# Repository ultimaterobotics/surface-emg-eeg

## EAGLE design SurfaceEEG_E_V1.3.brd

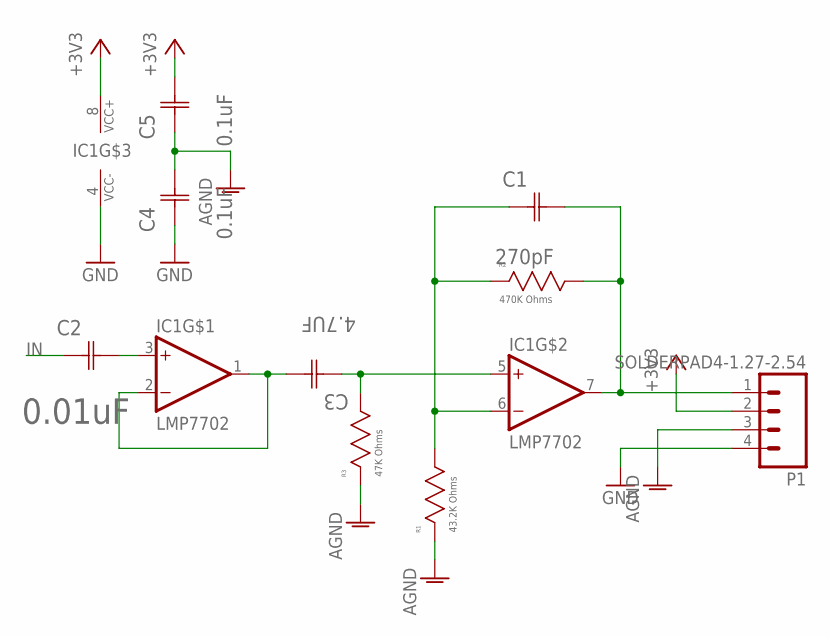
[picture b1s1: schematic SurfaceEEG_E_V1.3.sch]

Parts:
C1: 270pF; CAPC1608X90N
C2: 0.01uF; CAPC1005X60N
C3: 4.7UF; CAPC1608X90N
C4, C5: 0.1uF; CAPC1005X60N
IC1: LMP7702; VSSOP8
P1: SOLDERPAD4-1.27-2.54; SMD1,27-2,54
R1: 43.2K Ohms; RESC1608X60N
R2: 470K Ohms; RESC1608X60N
R3: 47K Ohms; RESC1608X60N

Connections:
+3V3: C5.1 (C2), IC1.8 (VCC+), P1.2
AGND: C4.1 (C2), C5.2 (C1), P1.3, R1.2 (R2), R3.2 (R2)
GND: C4.2 (C1), IC1.4 (VCC-), P1.4
IN: C2.1 (C1)
unnamed: C2.2 (C2), IC1.3 (IN+)
unnamed: C1.1 (C1), IC1.6 (IN-), R1.1 (R1), R2.2 (R2)
unnamed: C3.1 (C1), IC1.5 (IN+), R3.1 (R1)
unnamed: C1.2 (C2), IC1.7 (OUT), P1.1, R2.1 (R1)
SHIELD: C3.2 (C2), IC1.1 (OUT), IC1.2 (IN-)

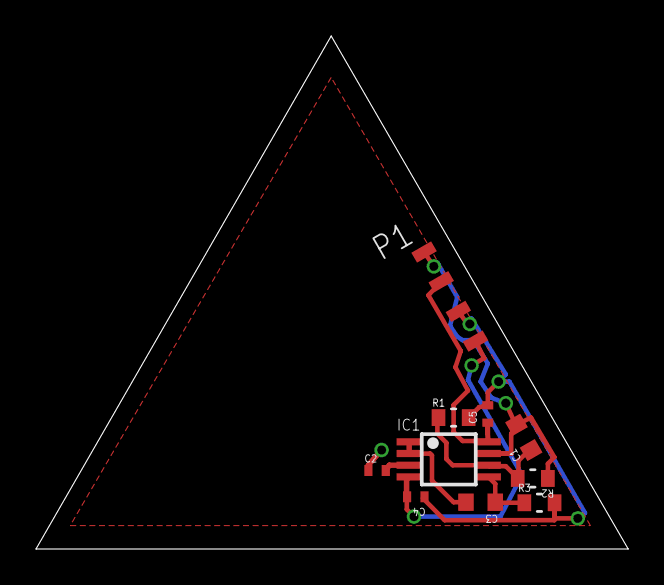
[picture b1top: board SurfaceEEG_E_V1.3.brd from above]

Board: 2 copper layers, 32.9 x 28.5 mm, 10 parts (0 on the bottom side), 8 nets.

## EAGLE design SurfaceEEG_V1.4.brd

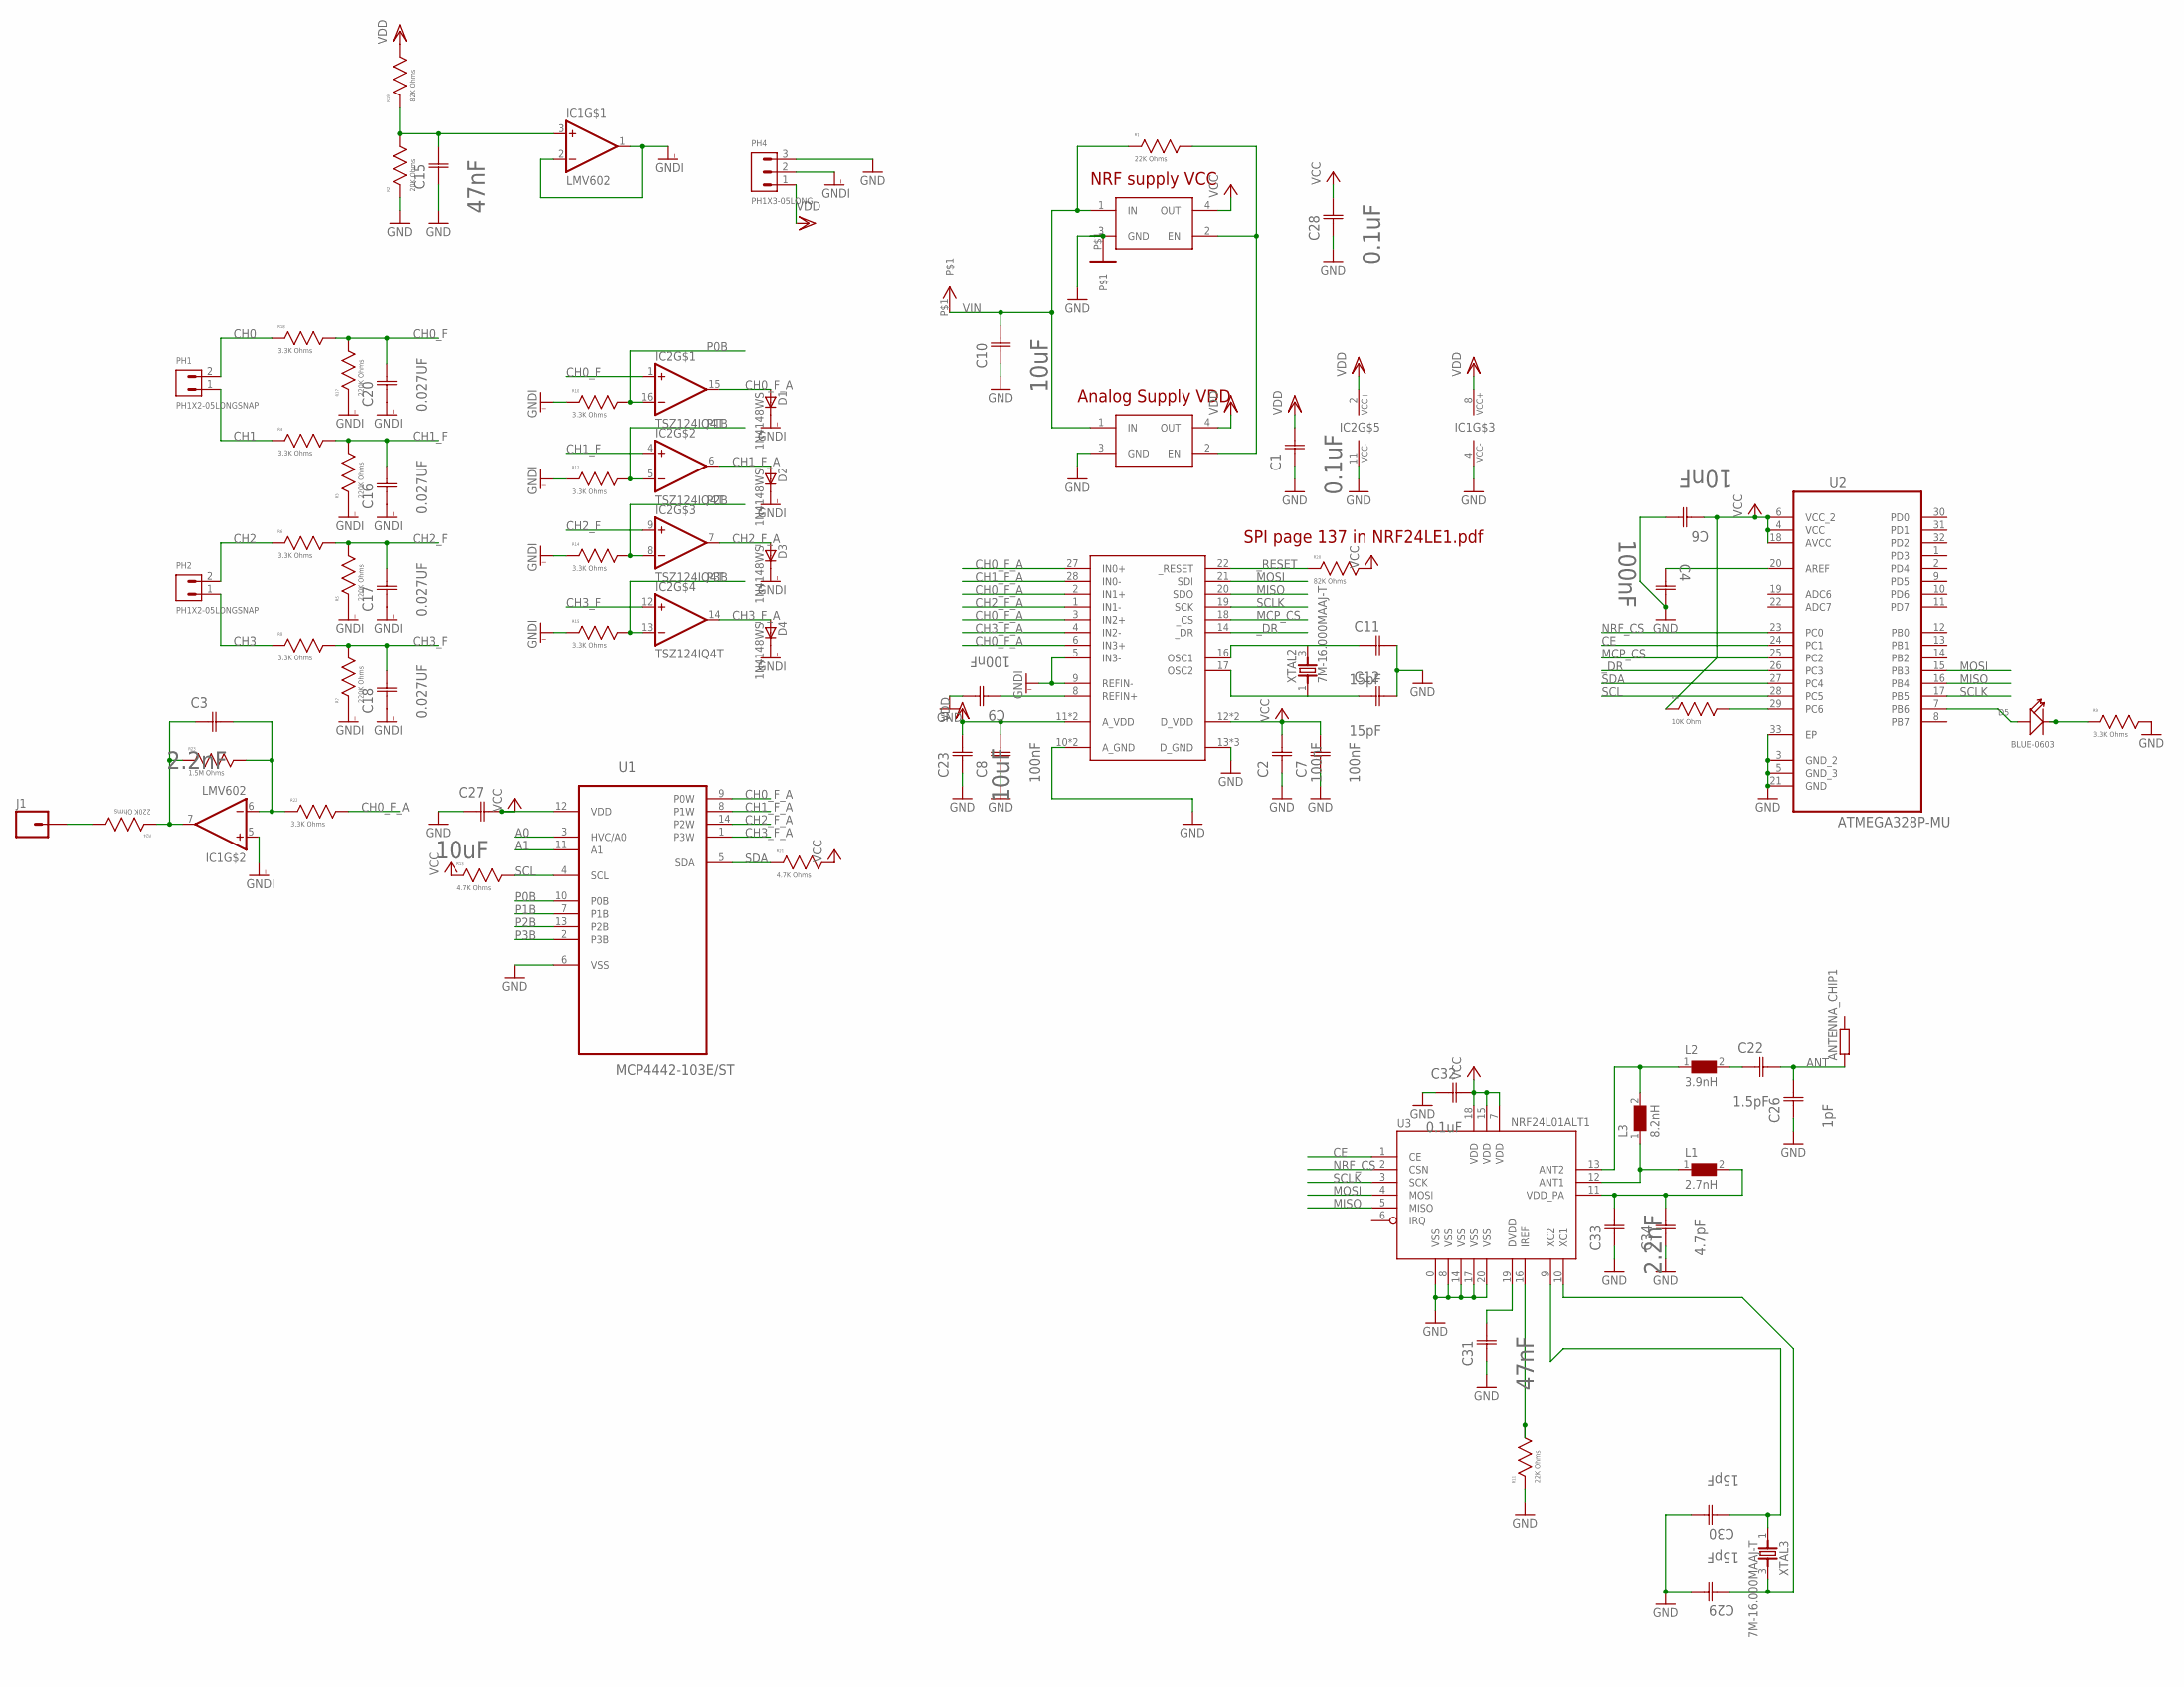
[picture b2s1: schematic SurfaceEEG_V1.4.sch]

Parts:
ANTENNA_CHIP1: R0805
C1, C28: 0.1uF; CAPC1608X85N
C2, C7, C8, C9: 100nF; CAPC1608X90N
C3, C33: 2.2nF; CAPC1005X60N
C4: 100nF; CAPC1608X85N
C6: 10nF; CAPC1608X85N
C10, C23, C27: 10uF; CAPC1608X85N
C11, C12, C29, C30: 15pF; CAPC1005X60N
C15, C31: 47nF; CAPC1608X85N
C16, C17, C18, C20: 0.027UF; CAPC1608X90N
C22: 1.5pF; CAPC1005X60N
C26: 1pF; CAPC1005X60N
C32: 0.1uF; CAPC1005X60N
C34: 4.7pF; CAPC1005X60N
D1, D2, D3, D4: 1N4148WS; SOD323F
D5: BLUE-0603; LED-0603
IC1: LMV602; VSSOP8
IC2: TSZ124IQ4T; QFN16
J1: M01SMD-4.5X1.5; PAD-1.5X4.5
L1: 2.7nH; WE-KI_0402A
L2: 3.9nH; WE-KI_0402A
L3: 8.2nH; WE-KI_0402A
PH1, PH2: PH1X2-05LONGSNAP; PHLS005-1-2
PH4: PH1X3-05LONG; PHL005-1-3
R1, R11: 22K Ohms; RESC1608X60N
R2: 20K Ohms; RESC1608X60N
R3, R5, R7, R17, R24: 220K Ohms; RESC1608X60N
R4, R6, R8, R9, R10, R12, R14, R15, R18, R22: 3.3K Ohms; RESC1608X60N
R13, R21: 4.7K Ohms; RESC1005X40N
R16: 10K Ohm; RESC1608X60N
R19, R20: 82K Ohms; RESC1608X60N
R23: 1.5M Ohms; RESC1608X60N
U1: MCP4442-103E/ST; SOP65P640X120-14N
U2: ATMEGA328P-MU; QFN50P500X500X100-33N
U3: NRF24L01ALT1; QFN20_ALT1
U$1, U$2: NCP103; UDFN4-1*1
U$3: MCP3912; QFN28
U$4: VCC; VCC-PAD
U$5: GND; GND-PAD
XTAL2, XTAL3: 7M-16.000MAAJ-T; TXC_7M-16.000MAAJ-T

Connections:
A0: U1.3 (HVC/A0)
A1: U1.11 (A1)
ANT: ANTENNA_CHIP1.1, C22.1 (C2), C26.1 (C2)
ANT1: L1.1, L3.1, U3.12 (ANT1)
ANT2: L2.1, L3.2, U3.13 (ANT2)
CE: U2.24 (PC1), U3.1 (CE)
CH0: PH1.2, R18.2 (R2)
CH0_F: C20.2 (C2), IC2.1 (IN+), R17.1 (R1), R18.1 (R1)
CH0_F_A: D1.A, IC2.15 (OUT), R22.1 (R1), U1.9 (P0W), U$3.2 (IN1+), U$3.3 (IN2+), U$3.6 (IN3+), U$3.27 (IN0+)
CH1: PH1.1, R4.2 (R2)
CH1_F: C16.2 (C2), IC2.4 (IN+), R3.1 (R1), R4.1 (R1)
CH1_F_A: D2.A, IC2.6 (OUT), U1.8 (P1W), U$3.28 (IN0-)
CH2: PH2.2, R6.2 (R2)
CH2_F: C17.2 (C2), IC2.9 (IN+), R5.1 (R1), R6.1 (R1)
CH2_F_A: D3.A, IC2.7 (OUT), U1.14 (P2W), U$3.1 (IN1-)
CH3: PH2.1, R8.2 (R2)
CH3_F: C18.2 (C2), IC2.12 (IN+), R7.1 (R1), R8.1 (R1)
CH3_F_A: D4.A, IC2.14 (OUT), U1.1 (P3W), U$3.4 (IN2-)
GND: C1.1 (C1), C2.1 (C1), C4.2 (C2), C6.2 (C2), C7.1 (C1), C8.1 (C1), C9.2 (C2), C10.1 (C1), C11.1 (C2), C12.1 (C2), C15.1 (C1), C23.1 (C1), C26.2 (C1), C27.1 (C1), C28.1 (C1), C29.1 (C2), C30.1 (C2), C31.1 (C1), C32.2 (C1), C33.1 (C1), C34.2 (C1), IC1.4 (VCC-), IC2.11 (VCC-), PH4.3, R2.2 (R2), R9.1 (R1), R11.2 (R2), U1.6 (VSS), U2.3 (GND_2), U2.5 (GND_3), U2.21 (GND), U2.33 (EP), U3.0 (VSS), U3.8 (VSS), U3.14 (VSS), U3.17 (VSS), U3.20 (VSS), U$1.3 (GND), U$2.3 (GND), U$3.10 (A_GND), U$3.13 (D_GND), U$3.15 (D_GND), U$3.23 (D_GND), U$3.26 (A_GND), U$5.P$1
GNDI: C16.1 (C1), C17.1 (C1), C18.1 (C1), C20.1 (C1), D1.C, D2.C, D3.C, D4.C, IC1.1 (OUT), IC1.2 (IN-), IC1.5 (IN+), PH4.2, R3.2 (R2), R5.2 (R2), R7.2 (R2), R10.2 (R2), R12.2 (R2), R14.2 (R2), R15.2 (R2), R17.2 (R2), U$3.5 (IN3-), U$3.9 (REFIN-)
MCP_CS: U2.25 (PC2), U$3.18 (_CS)
MISO: U2.16 (PB4), U3.5 (MISO), U$3.20 (SDO)
MOSI: U2.15 (PB3), U3.4 (MOSI), U$3.21 (SDI)
unnamed: D5.+, U2.7 (PB6)
unnamed: D5.-, R9.2 (R2)
unnamed: C3.2 (C2), IC1.6 (IN-), R22.2 (R2), R23.1 (R1)
unnamed: R1.1 (R1), U$1.2 (EN), U$2.2 (EN)
unnamed: C3.1 (C1), IC1.7 (OUT), R23.2 (R2), R24.2 (R2)
unnamed: C4.1 (C1), U2.20 (AREF)
unnamed: C30.2 (C1), U3.9 (XC2), XTAL3.1
unnamed: C29.2 (C1), U3.10 (XC1), XTAL3.3
unnamed: J1.P$1, R24.1 (R1)
unnamed: C9.1 (C1), U$3.8 (REFIN+)
unnamed: C22.2 (C1), L2.2
unnamed: C11.2 (C1), U$3.16 (OSC1), XTAL2.3
unnamed: C12.2 (C1), U$3.17 (OSC2), XTAL2.1
unnamed: C33.2 (C2), C34.1 (C2), L1.2, U3.11 (VDD_PA)
unnamed: C15.2 (C2), IC1.3 (IN+), R2.1 (R1), R19.2 (R2)
unnamed: R11.1 (R1), U3.16 (IREF)
unnamed: C31.2 (C2), U3.19 (DVDD)
NRF_CS: U2.23 (PC0), U3.2 (CSN)
P0B: IC2.16 (IN-), R10.1 (R1), U1.10 (P0B)
P1B: IC2.5 (IN-), R12.1 (R1), U1.7 (P1B)
P2B: IC2.8 (IN-), R14.1 (R1), U1.13 (P2B)
P3B: IC2.13 (IN-), R15.1 (R1), U1.2 (P3B)
RESET: R16.1 (R1), U2.29 (PC6)
SCL: R13.1 (R1), U1.4 (SCL), U2.28 (PC5)
SCLK: U2.17 (PB5), U3.3 (SCK), U$3.19 (SCK)
SDA: R21.2 (R2), U1.5 (SDA), U2.27 (PC4)
VCC: C2.2 (C2), C6.1 (C1), C7.2 (C2), C27.2 (C2), C28.2 (C2), C32.1 (C2), R13.2 (R2), R16.2 (R2), R20.1 (R1), R21.1 (R1), U1.12 (VDD), U2.4 (VCC), U2.6 (VCC_2), U2.18 (AVCC), U3.7 (VDD), U3.15 (VDD), U3.18 (VDD), U$1.4 (OUT), U$3.12 (D_VDD), U$3.24 (D_VDD)
VDD: C1.2 (C2), C8.2 (C2), C23.2 (C2), IC1.8 (VCC+), IC2.2 (VCC+), PH4.1, R19.1 (R1), U$2.4 (OUT), U$3.11 (A_VDD), U$3.25 (A_VDD)
VIN: C10.2 (C2), R1.2 (R2), U$1.1 (IN), U$2.1 (IN), U$4.P$1
_DR: U2.26 (PC3), U$3.14 (_DR)
_RESET: R20.2 (R2), U$3.22 (_RESET)

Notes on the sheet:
SPI page 137 in NRF24LE1.pdf
NRF supply VCC
Analog Supply VDD

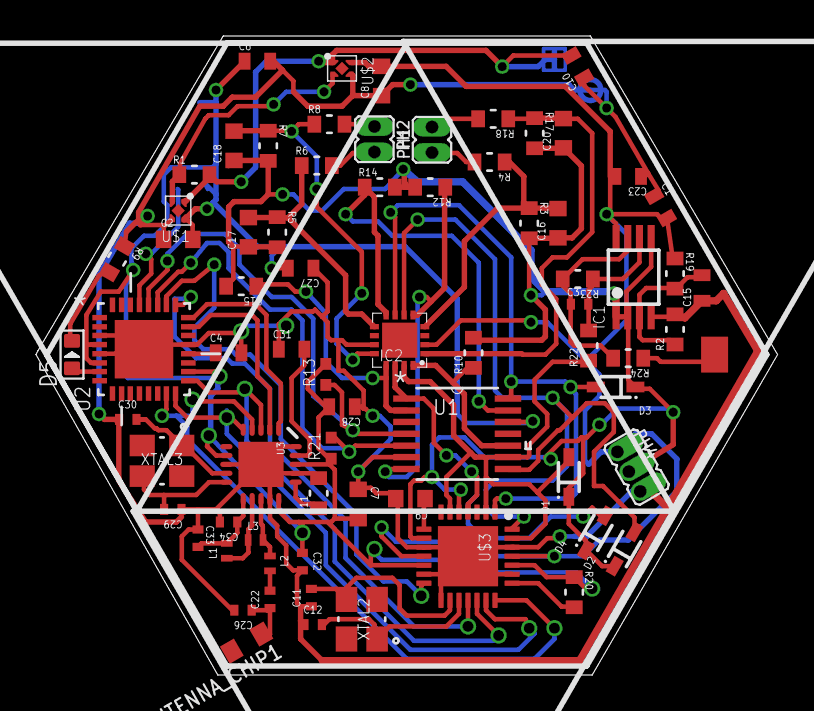
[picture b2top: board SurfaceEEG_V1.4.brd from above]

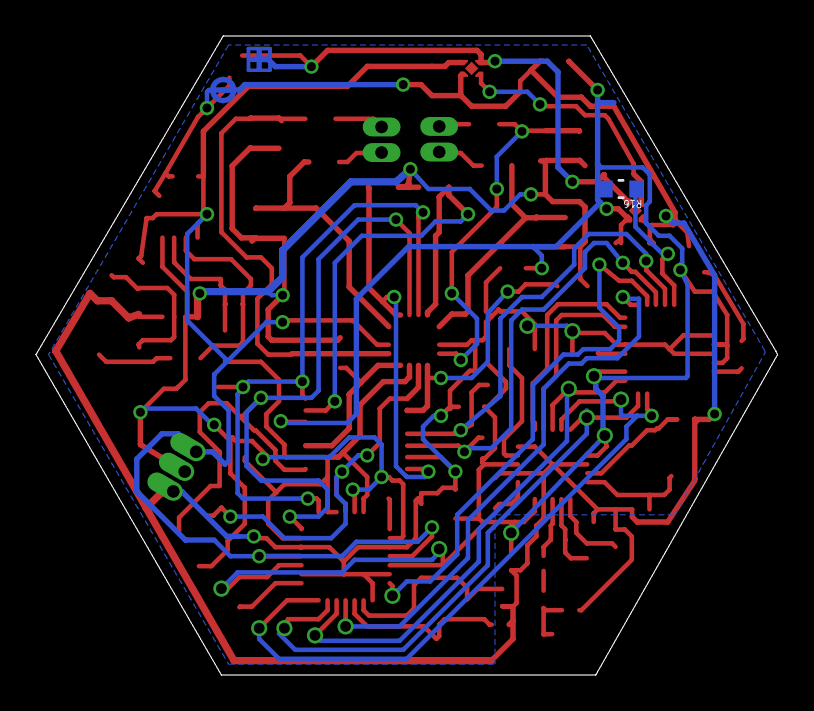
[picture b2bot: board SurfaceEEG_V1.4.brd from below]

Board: 2 copper layers, 41.2 x 35.5 mm, 76 parts (3 on the bottom side), 52 nets.

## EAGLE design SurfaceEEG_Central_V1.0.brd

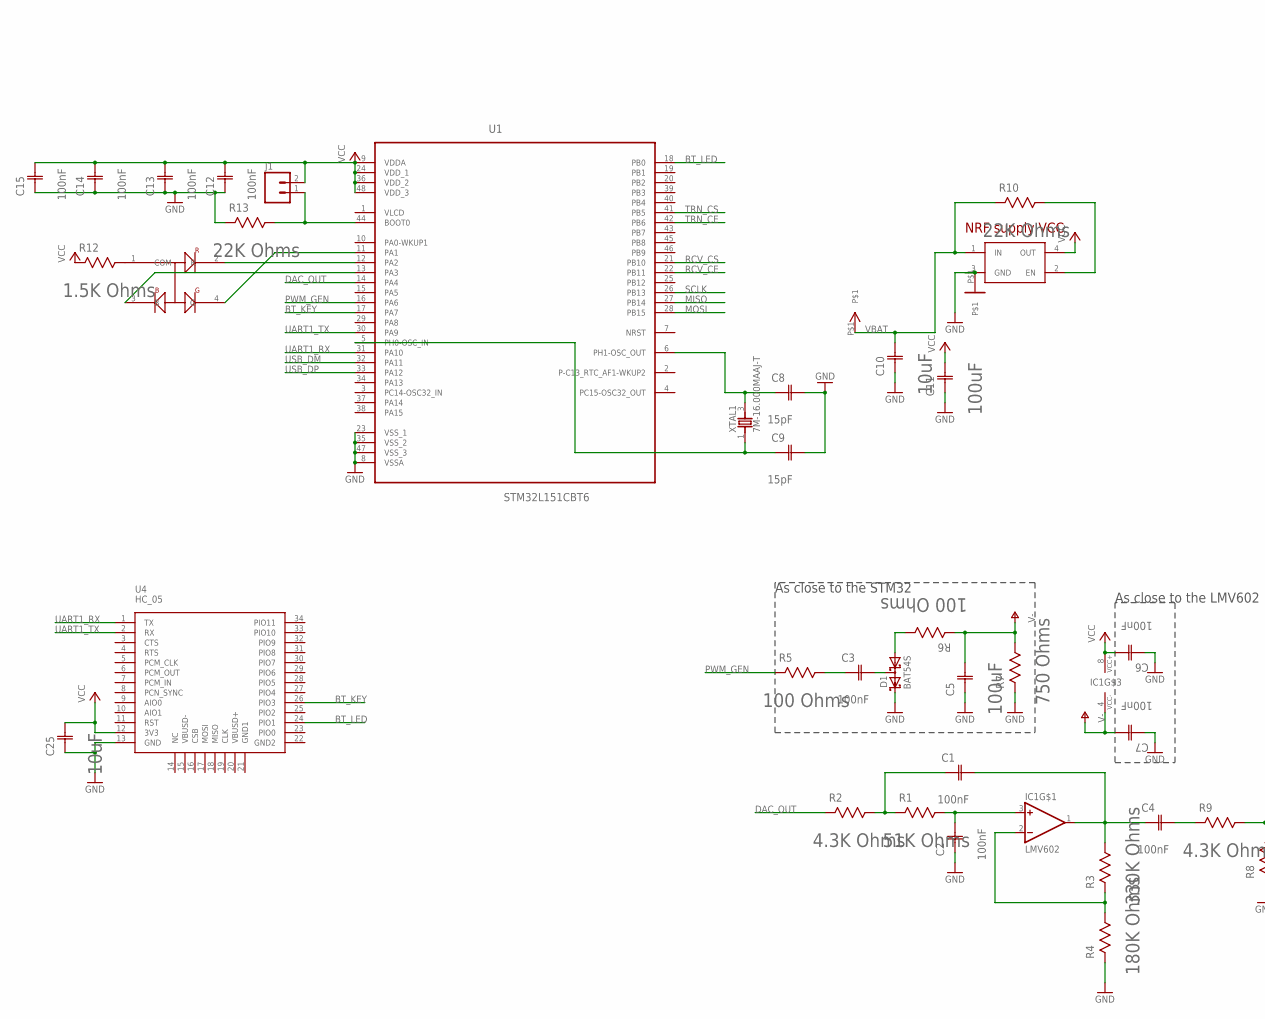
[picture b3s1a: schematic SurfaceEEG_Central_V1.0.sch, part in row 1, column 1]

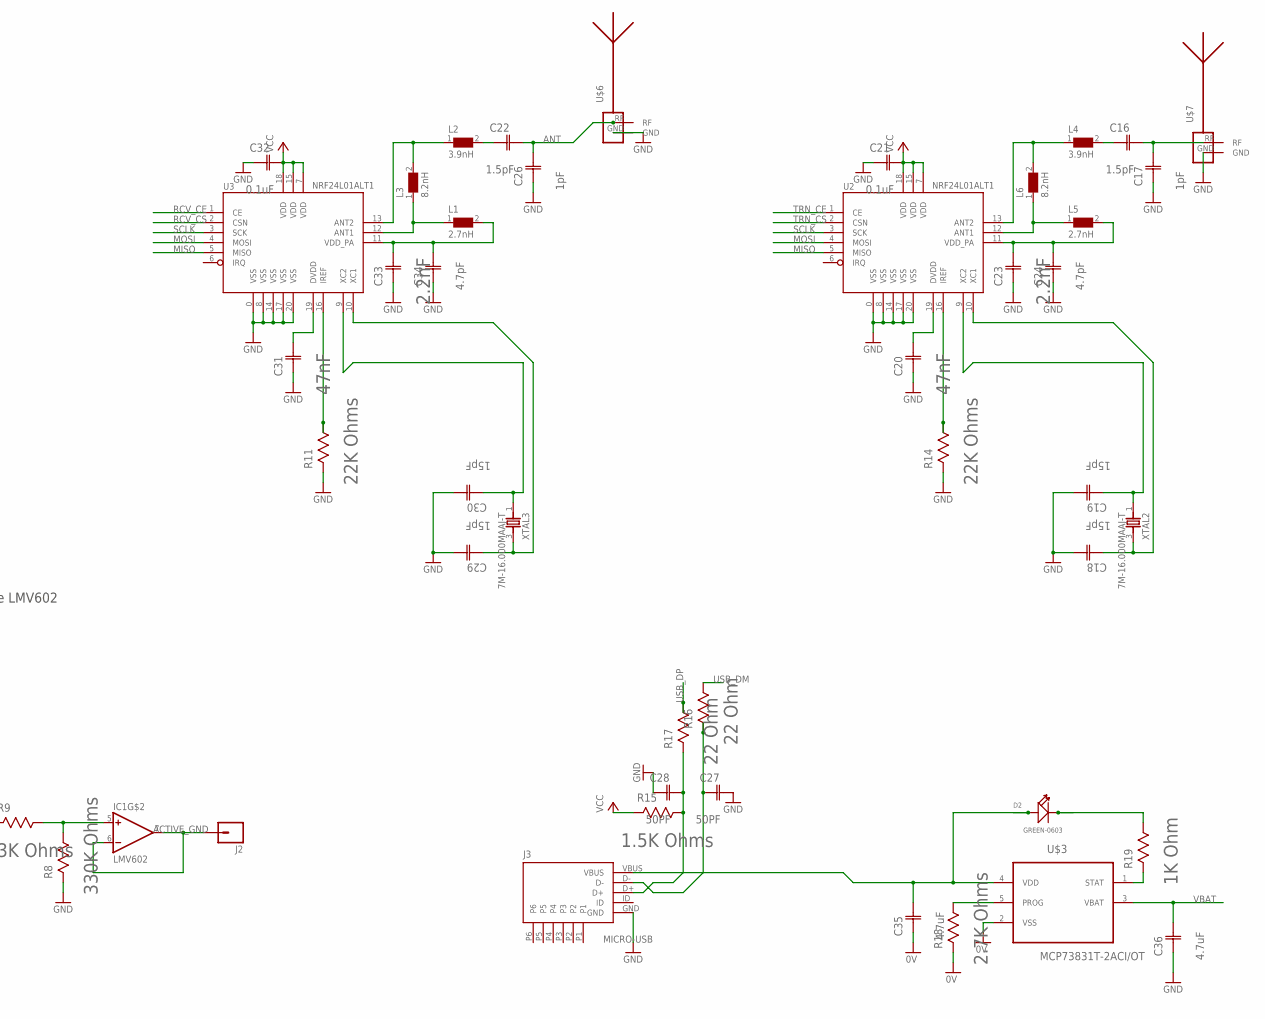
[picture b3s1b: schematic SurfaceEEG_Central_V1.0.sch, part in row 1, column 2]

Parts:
C1, C2, C3, C4, C6, C7, C12, C13, C14, C15: 100nF; CAPC1608X90N
C5, C11: 100uF; CAPC3216X180N
C8, C9, C18, C19, C29, C30: 15pF; CAPC1005X60N
C10, C25: 10uF; CAPC1608X85N
C16, C22: 1.5pF; CAPC1005X60N
C17, C26: 1pF; CAPC1005X60N
C20, C31: 47nF; CAPC1608X85N
C21, C32: 0.1uF; CAPC1005X60N
C23, C33: 2.2nF; CAPC1005X60N
C24, C34: 4.7pF; CAPC1005X60N
C27, C28: 50PF; CAPC1608X90N
C35, C36: 4.7uF; CAPC2013X152N
D1: BAT54S; SOT23
D2: GREEN-0603; LED-0603
IC1: LMV602; VSSOP8
J1: M02PTH; 1X02
J2: M01SMD-4.5X1.5; PAD-1.5X4.5
J3: MICRO-USB; MICRO_USB
L1, L5: 2.7nH; WE-KI_0402A
L2, L4: 3.9nH; WE-KI_0402A
L3, L6: 8.2nH; WE-KI_0402A
R1: 51K Ohms; RESC1608X60N
R2, R9: 4.3K Ohms; RESC1608X60N
R3, R8: 330K Ohms; RESC1608X60N
R4: 180K Ohms; RESC1608X60N
R5, R6: 100 Ohms; RESC1608X60N
R7: 750 Ohms; RESC1608X60N
R10, R11, R13, R14: 22K Ohms; RESC1608X60N
R12, R15: 1.5K Ohms; RESC1608X60N
R16, R17: 22 Ohm; RESC1608X60N
R18: 2.7K Ohms; RESC1608X60N
R19: 1K Ohm; RESC1608X60N
U1: STM32L151CBT6; QFP50P900X900X160-48N
U2, U3: NRF24L01ALT1; QFN20_ALT1
U4: HC_05; BLUETOOTH_SMD
U$1: NCP103; UDFN4-1*1
U$2: RGB-LED; 1615-RGB-LED
U$3: MCP73831T-2ACI/OT; SOT95P280X145-5N
U$4: VCC; VCC-PAD
U$5: GND; GND-PAD
U$6: ANTENNA_1LEFT; SWRA117D_LEFT
U$7: ANTENNA_1RIGHT; SWRA117D_RIGHT
XTAL1, XTAL2, XTAL3: 7M-16.000MAAJ-T; TXC_7M-16.000MAAJ-T

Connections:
0V: C35.1 (C1), R18.2 (R2), U$3.2 (VSS)
ACTIVE_GND: IC1.6 (IN-), IC1.7 (OUT), J2.P$1
ANT: C22.1 (C2), C26.1 (C2), U$6.RF
ANT1: L1.1, L3.1, U3.12 (ANT1)
ANT2: L2.1, L3.2, U3.13 (ANT2)
ANT3: L4.1, L6.2, U2.13 (ANT2)
ANT4: L5.1, L6.1, U2.12 (ANT1)
BT_KEY: U1.17 (PA7), U4.26 (PIO3)
BT_LED: U1.18 (PB0), U4.24 (PIO1)
DAC_OUT: R2.2 (R2), U1.14 (PA4)
GND: C2.1 (C1), C5.1 (C1), C6.1 (C1), C7.1 (C1), C8.1 (C2), C9.1 (C2), C10.1 (C1), C11.1 (C1), C12.1 (C1), C13.1 (C1), C14.1 (C1), C15.1 (C1), C17.2 (C1), C18.1 (C2), C19.1 (C2), C20.1 (C1), C21.2 (C1), C23.1 (C1), C24.2 (C1), C25.1 (C1), C26.2 (C1), C27.2 (C2), C28.1 (C1), C29.1 (C2), C30.1 (C2), C31.1 (C1), C32.2 (C1), C33.1 (C1), C34.2 (C1), C36.1 (C1), D1.2 (C2), J3.GND, R4.2 (R2), R7.2 (R2), R8.2 (R2), R11.2 (R2), R13.2 (R2), R14.2 (R2), U1.8 (VSSA), U1.23 (VSS_1), U1.35 (VSS_2), U1.47 (VSS_3), U2.0 (VSS), U2.8 (VSS), U2.14 (VSS), U2.17 (VSS), U2.20 (VSS), U3.0 (VSS), U3.8 (VSS), U3.14 (VSS), U3.17 (VSS), U3.20 (VSS), U4.13 (GND), U$1.3 (GND), U$5.P$1, U$6.GND, U$7.GND
MISO: U1.27 (PB14), U2.5 (MISO), U3.5 (MISO)
MOSI: U1.28 (PB15), U2.4 (MOSI), U3.4 (MOSI)
unnamed: C1.1 (C1), R1.2 (R2), R2.1 (R1)
unnamed: IC1.2 (IN-), R3.2 (R2), R4.1 (R1)
unnamed: C1.2 (C2), C4.1 (C1), IC1.1 (OUT), R3.1 (R1)
unnamed: C2.2 (C2), IC1.3 (IN+), R1.1 (R1)
unnamed: IC1.5 (IN+), R8.1 (R1), R9.1 (R1)
unnamed: C4.2 (C2), R9.2 (R2)
unnamed: C3.1 (C1), R5.1 (R1)
unnamed: C3.2 (C2), D1.3 (C1A2)
unnamed: D1.1 (A1), R6.1 (R1)
unnamed: C29.2 (C1), U3.10 (XC1), XTAL3.3
unnamed: R10.1 (R1), U$1.2 (EN)
unnamed: C30.2 (C1), U3.9 (XC2), XTAL3.1
unnamed: C22.2 (C1), L2.2
unnamed: C8.2 (C1), U1.6 (PH1-OSC_OUT), XTAL1.3
unnamed: C9.2 (C1), U1.5 (PH0-OSC_IN), XTAL1.1
unnamed: C33.2 (C2), C34.1 (C2), L1.2, U3.11 (VDD_PA)
unnamed: U1.12 (PA2), U$2.2 (R)
unnamed: U1.13 (PA3), U$2.3 (B)
unnamed: R11.1 (R1), U3.16 (IREF)
unnamed: C31.2 (C2), U3.19 (DVDD)
unnamed: U1.11 (PA1), U$2.4 (G)
unnamed: R12.1 (R1), U$2.1 (COM)
unnamed: J1.1, R13.1 (R1), U1.44 (BOOT0)
unnamed: C18.2 (C1), U2.10 (XC1), XTAL2.3
unnamed: C23.2 (C2), C24.1 (C2), L5.2, U2.11 (VDD_PA)
unnamed: R14.1 (R1), U2.16 (IREF)
unnamed: C20.2 (C2), U2.19 (DVDD)
unnamed: C16.2 (C1), L4.2
unnamed: C19.2 (C1), U2.9 (XC2), XTAL2.1
unnamed: C16.1 (C2), C17.1 (C2), U$7.RF
unnamed: C35.2 (C2), D2.+, J3.VBUS, U$3.4 (VDD)
unnamed: C28.2 (C2), J3.D+, R15.1 (R1), R17.2 (R2)
unnamed: C27.1 (C1), J3.D-, R16.2 (R2)
unnamed: R18.1 (R1), U$3.5 (PROG)
unnamed: D2.-, R19.1 (R1)
unnamed: R19.2 (R2), U$3.1 (STAT)
PWM_GEN: R5.2 (R2), U1.16 (PA6)
RCV_CE: U1.22 (PB11), U3.1 (CE)
RCV_CS: U1.21 (PB10), U3.2 (CSN)
SCLK: U1.26 (PB13), U2.3 (SCK), U3.3 (SCK)
TRN_CE: U1.42 (PB6), U2.1 (CE)
TRN_CS: U1.41 (PB5), U2.2 (CSN)
UART1_RX: U1.31 (PA10), U4.1 (TX)
UART1_TX: U1.30 (PA9), U4.2 (RX)
USB_DM: R16.1 (R1), U1.32 (PA11)
USB_DP: R17.1 (R1), U1.33 (PA12)
V-: C5.2 (C2), C7.2 (C2), IC1.4 (VCC-), R6.2 (R2), R7.1 (R1)
VBAT: C10.2 (C2), C36.2 (C2), R10.2 (R2), U$1.1 (IN), U$3.3 (VBAT), U$4.P$1
VCC: C6.2 (C2), C11.2 (C2), C12.2 (C2), C13.2 (C2), C14.2 (C2), C15.2 (C2), C21.1 (C2), C25.2 (C2), C32.1 (C2), IC1.8 (VCC+), J1.2, R12.2 (R2), R15.2 (R2), U1.9 (VDDA), U1.24 (VDD_1), U1.36 (VDD_2), U1.48 (VDD_3), U2.7 (VDD), U2.15 (VDD), U2.18 (VDD), U3.7 (VDD), U3.15 (VDD), U3.18 (VDD), U4.12 (3V3), U$1.4 (OUT)
VLCD: U1.1 (VLCD)

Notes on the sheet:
As close to the STM32
As close to the LMV602
NRF supply VCC

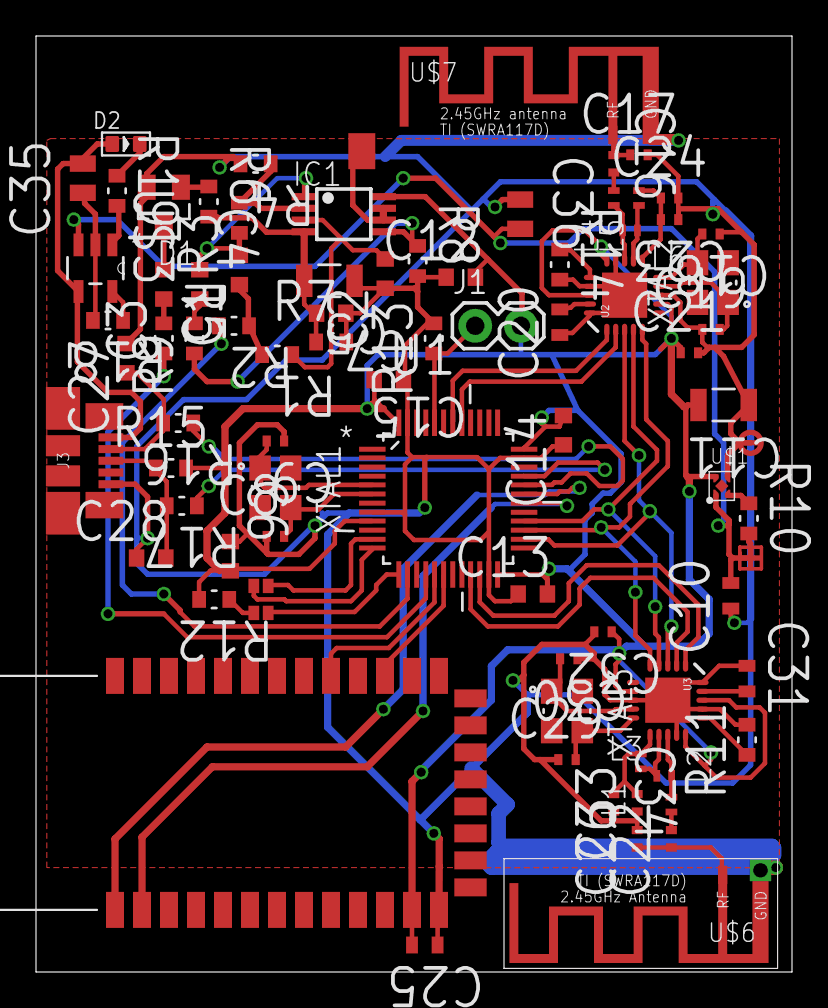
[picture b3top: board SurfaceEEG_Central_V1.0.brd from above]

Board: 2 copper layers, 42.0 x 52.0 mm, 81 parts (0 on the bottom side), 62 nets.

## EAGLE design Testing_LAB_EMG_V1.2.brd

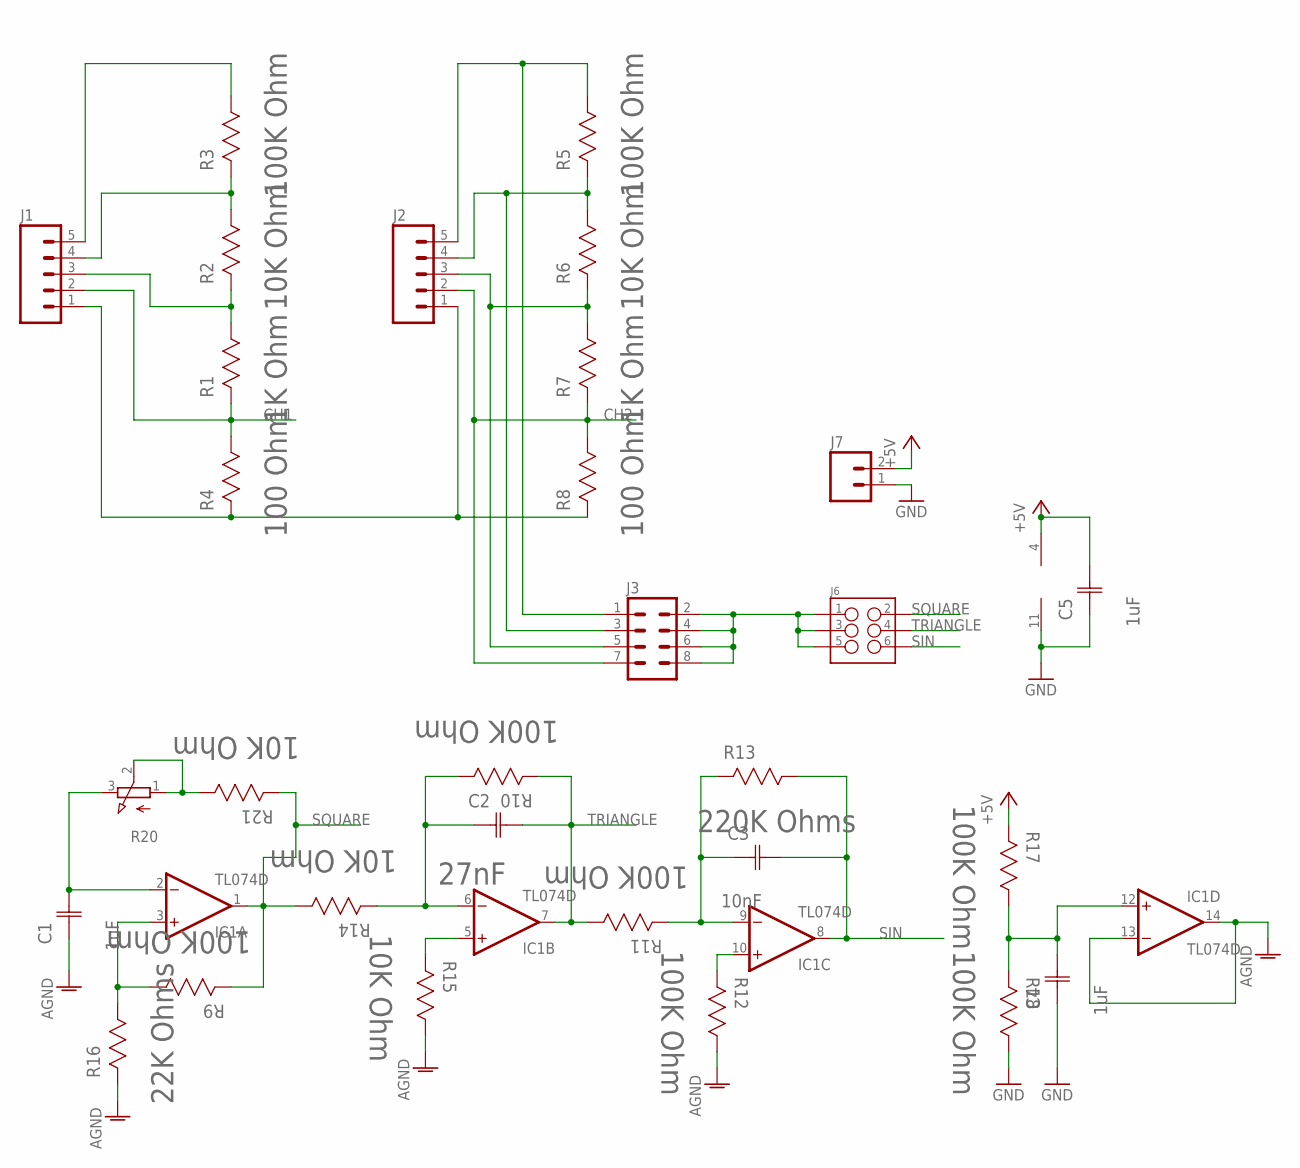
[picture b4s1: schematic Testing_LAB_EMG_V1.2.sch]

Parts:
C1, C4, C5: 1uF; CAPC1608X94N
C2: 27nF; CAPC1005X60N
C3: 10nF; CAPC1608X90N
IC1: TL074D; SO14
J1, J2: M05PTH; 1X05
J3: M04X2; 2X4
J6: M03X2NO_SILK; 2X3-NS
J7: M02PTH; 1X02
R1, R7: 1K Ohm; RESC1608X60N
R2, R6, R14, R15, R21: 10K Ohm; RESC1608X60N
R3, R5, R9, R10, R11, R12, R17, R18: 100K Ohm; RESC1608X60N
R4, R8: 100 Ohm; RESC1608X60N
R13: 220K Ohms; RESC1608X60N
R16: 22K Ohms; RESC1608X60N
R20: 3RP/1610N

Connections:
+5V: C5.2 (C2), IC1.4 (V+), J7.2, R17.2 (R2)
AGND: C1.1 (C1), IC1.13 (-IN), IC1.14 (OUT), R12.1 (R1), R15.1 (R1), R16.2 (R2)
CH1: J1.2, R1.2 (R2), R4.1 (R1)
CH2: J2.2, J3.7, R7.2 (R2), R8.1 (R1)
GND: C4.1 (C1), C5.1 (C1), IC1.11 (V-), J7.1, R18.1 (R1)
unnamed: J1.5, R3.1 (R1)
unnamed: J1.4, R2.1 (R1), R3.2 (R2)
unnamed: J1.3, R1.1 (R1), R2.2 (R2)
unnamed: J2.4, J3.3, R5.2 (R2), R6.1 (R1)
unnamed: J1.1, J2.1, R4.2 (R2), R8.2 (R2)
unnamed: J2.3, J3.5, R6.2 (R2), R7.1 (R1)
unnamed: J2.5, J3.1, R5.1 (R1)
unnamed: C4.2 (C2), IC1.12 (+IN), R17.1 (R1), R18.2 (R2)
unnamed: R20.1 (A), R20.2 (S), R21.1 (R1)
unnamed: J3.2, J3.4, J3.6, J3.8, J6.1, J6.3, J6.5
unnamed: IC1.3 (+IN), R9.1 (R1), R16.1 (R1)
unnamed: C1.2 (C2), IC1.2 (-IN), R20.3 (E)
unnamed: IC1.5 (+IN), R15.2 (R2)
unnamed: C2.1 (C1), IC1.6 (-IN), R10.1 (R1), R14.2 (R2)
unnamed: IC1.10 (+IN), R12.2 (R2)
unnamed: C3.1 (C1), IC1.9 (-IN), R11.2 (R2), R13.2 (R2)
SIN: C3.2 (C2), IC1.8 (OUT), J6.6, R13.1 (R1)
SQUARE: IC1.1 (OUT), J6.2, R9.2 (R2), R14.1 (R1), R21.2 (R2)
TRIANGLE: C2.2 (C2), IC1.7 (OUT), J6.4, R10.2 (R2), R11.1 (R1)

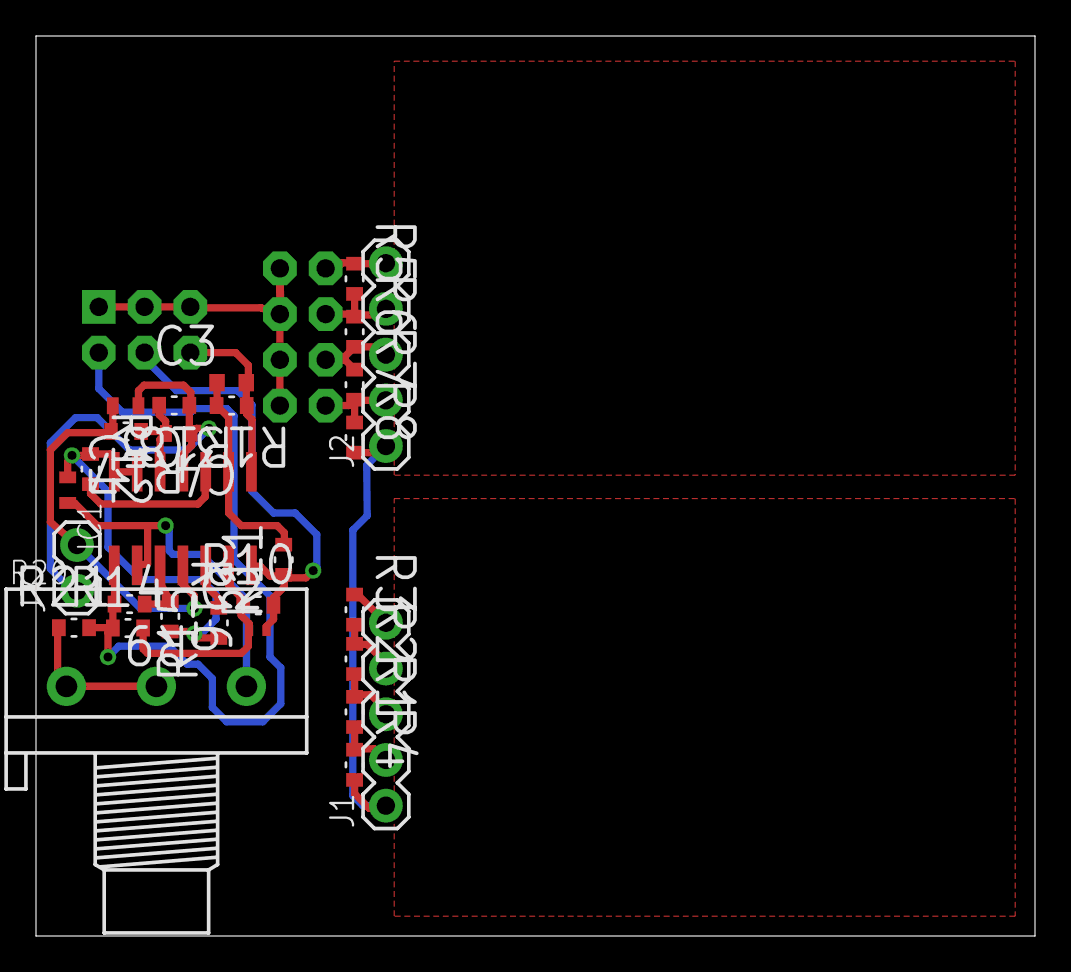
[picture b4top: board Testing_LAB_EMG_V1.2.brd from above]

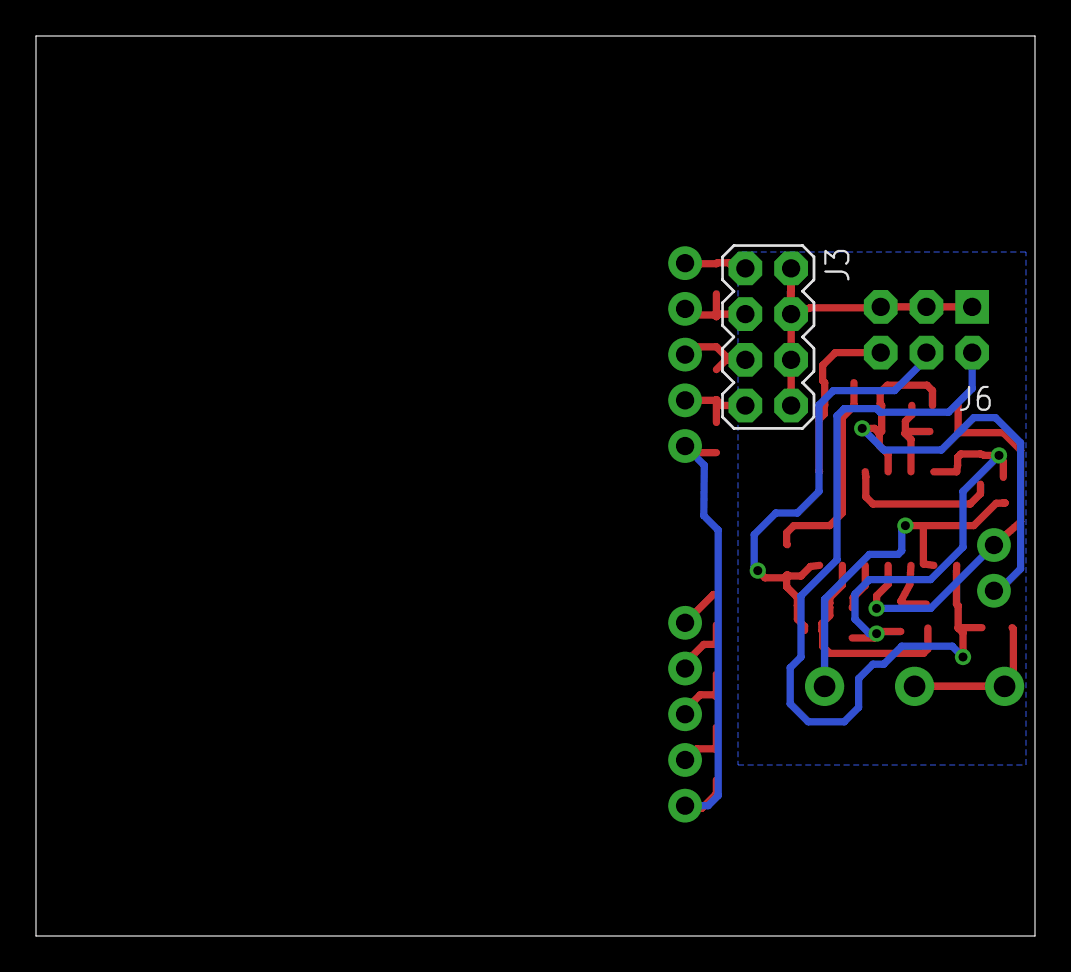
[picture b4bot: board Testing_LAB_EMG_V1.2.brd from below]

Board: 2 copper layers, 55.5 x 50.0 mm, 31 parts (2 on the bottom side), 24 nets.

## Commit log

2016-12-02 Added current version of EMG module
2016-12-02 Replaced components with ones from our libraries
2016-12-02 Added RF antenna schematics
2016-12-02 Add crystal 16 MHz
    Add crystal 16 MHz for NRF24LE1
2016-12-05 Created almost finished board, fixed schematics
    Schematics was switched for 3 differential + 1 relative to ground measurements, board was designed accordingly
2016-12-05 Add active electrodes V1.1
    I think that this connector will be huge.
2016-12-05 Finished PCB and updated schematics
    Added headers for sensor board connection and placed/routed remaining caps, optimized everything
2016-12-05 Changed RF chip to 24-pin version
    We realized too late that our actual chips were in 24-pin packages...
2016-12-05 Add high pass filter to active electrode
    Add high pass filter and trace PCB V1.2
2016-12-07 Added SurfaceEEG HUB
    Added schematic and board for SurfaceEEG_HUB_V1.0
2016-12-07 Started version 1.4 with atmega328
2016-12-07 Fixed hub module according to DRC
2016-12-07 Fixed unrouted wire
2016-12-07 Added new solder pad
    Added new SOLDERPAD4-1.27-2.54 to SurfaceEEG_Hub
2016-12-07 Updated SurfaceEEG_E
    Updated SurfaceEEG_E to V1.3. Replaced solder pads. Improved layout and
    checked DRC.
2016-12-08 Version 1.4 with atmega328 and hrf24L01 ready
2016-12-08 Updated all boards in order to comply with DRC
2016-12-11 Added active ground
    Ku = 50 dB on 50 Hz
    A low-pass filter = -6 dB/octave, 1 kHz = 26 dB, 22 kHz = 0 dB
2016-12-11 added led
2016-12-11 Module active ground completed
2016-12-11 Added SurfaceEEG_Central and active ground schematic
    V1.0
    - Low-pass filter II-order, Fs = 100 Hz, Ku = 2.83;
    - High-pass filter I-order, Fs = 5 Hz, Ku = 1;
    - Voltage inverter: 50 kHz, Out = -1.5 V, 200 uV noize p-p, set up time
    300 ms;
2016-12-12 Central unit completed, testing module added
2016-12-24 Board changed after library changes
    After making fonts smaller, the board have changed
2016-12-27 Boards changed after changing fonts
    That's it.

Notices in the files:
parts and their libraries:
SparkFun-Connectors: Licensing: Creative Commons ShareAlike 4.0 International - https://creativecommons.org/licenses/by-sa/4.0
ELL-i-Passives: Originally copied from SparkFun-Passives.lbr, under SparkFun Creative Commons license.
